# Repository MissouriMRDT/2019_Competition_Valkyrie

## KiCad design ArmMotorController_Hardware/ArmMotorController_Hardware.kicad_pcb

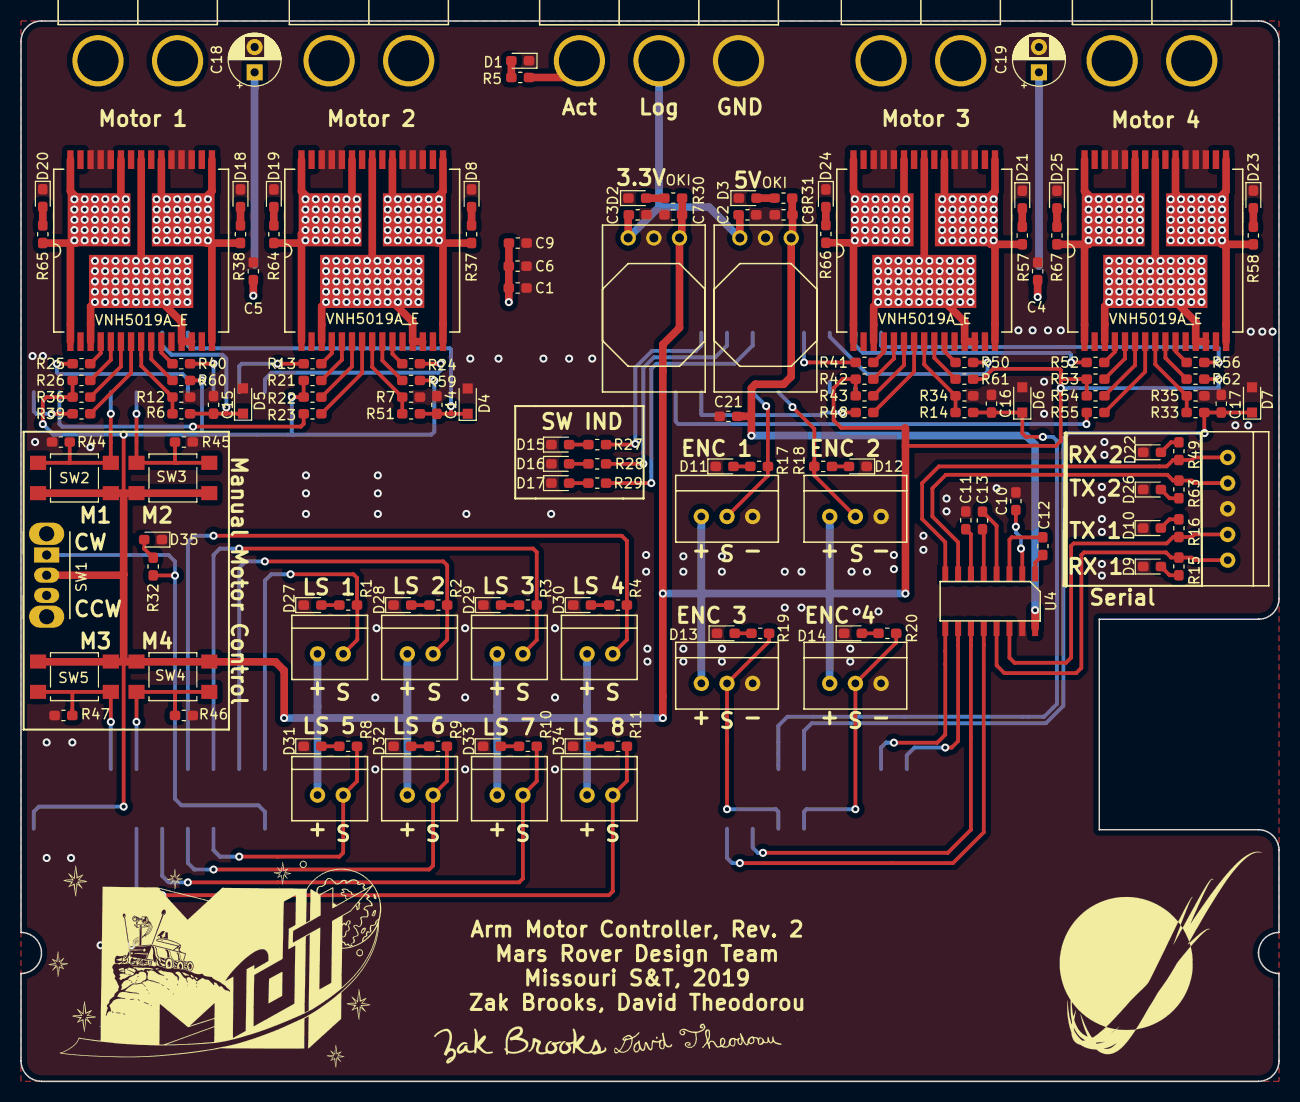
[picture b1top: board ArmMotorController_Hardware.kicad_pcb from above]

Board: 2 copper layers, 124.5 x 104.9 mm, 153 parts (0 on the bottom side), 122 nets.

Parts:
C1, C10, C11, C12, C13: .1u; C_0603_1608Metric_Pad1.05x0.95mm_HandSolder
C2, C3, C4, C5, C6, C7, C8, C9: 10u; C_0603_1608Metric_Pad1.05x0.95mm_HandSolder
C14, C15, C16, C17: 33nF; C_0603_1608Metric_Pad1.05x0.95mm_HandSolder
C18, C19: 47u; CP_Radial_D5.0mm_P2.50mm
C21: 10uF; C_0603_1608Metric_Pad1.05x0.95mm_HandSolder
Conn1: Anderson-3; Anderson_3_Horizontal_Side_by_Side
Conn3: Limit_Switch_1; MOLEX_SL_02_Vertical
Conn4: Limit_Switch_2; MOLEX_SL_02_Vertical
Conn5: Limit_Switch_3; MOLEX_SL_02_Vertical
Conn6: Limit_Switch_4; MOLEX_SL_02_Vertical
Conn7: Limit_Switch_5; MOLEX_SL_02_Vertical
Conn8: Limit_Switch_6; MOLEX_SL_02_Vertical
Conn9: Limit_Switch_7; MOLEX_SL_02_Vertical
Conn10: Limit_Switch_8; MOLEX_SL_02_Vertical
Conn11: Molex_SL_05; MOLEX_SL_05_Vertical
Conn12: Encoder_1; MOLEX_SL_03_Vertical
Conn13: Encoder_2; MOLEX_SL_03_Vertical
Conn14: Encoder_3; MOLEX_SL_03_Vertical
Conn15: Encoder_4; MOLEX_SL_03_Vertical
Conn16, Conn17, Conn18, Conn19: AndersonPP; Anderson_2_Horizontal_Side_by_Side
D1, D2, D3, D8, D9, D10, D11, D12, D13, D14, D15, D16, D17, D18, D19, D20, D21, D22, D23, D24, D25, D26, D27, D28, D29, D30, D31, D32, D33, D34, D35: LED; LED_0603_1608Metric_Pad1.05x0.95mm_HandSolder
D4, D5, D6, D7: D_Zener; D_SOD-323_HandSoldering
R1, R2, R3, R4, R5, R8, R9, R10, R11, R15, R16, R17, R18, R19, R20, R27, R28, R29, R30, R31, R32, R44, R45, R46, R47, R49, R63: 500; R_0603_1608Metric_Pad1.05x0.95mm_HandSolder
R6, R14, R33, R51: 10k; R_0603_1608Metric_Pad1.05x0.95mm_HandSolder
R7, R12, R13, R21, R23, R24, R25, R26, R34, R35, R39, R40, R41, R42, R48, R50, R52, R53, R55, R56, R59, R60, R61, R62: 1k; R_0603_1608Metric_Pad1.05x0.95mm_HandSolder
R22, R36, R43, R54: 0; R_0603_1608Metric_Pad1.05x0.95mm_HandSolder
R37, R38, R57, R58, R64, R65, R66, R67: 1.5k; R_0603_1608Metric_Pad1.05x0.95mm_HandSolder
SW1: SW_SPDT; SW_CuK_OS102011MA1QN1_SPDT_Angled
SW2, SW3, SW4, SW5: SW_Push; SW_SPST_TL3305A
U1, U2: OKI; OKI_Horizontal
U3: TM4C129E_Launchpad; TM4C129E_Launchpad_FULL_SMD_BOTTOM
U4: MAX_3232; SOIC_16_3.9x9.9mm_Pitch1.27mm
U5, U6, U7, U8: VNH5019A_E; MultiPowerSO_30

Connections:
12vLog: C2.2, C3.2, Conn1.2, U1.1, U2.1
+3V3: C7.2, Conn3.1, Conn4.1, Conn5.1, Conn6.1, Conn7.1, Conn8.1, Conn9.1, Conn10.1, Conn12.1, Conn13.1, Conn14.1, Conn15.1, R21.2, R22.2, R26.2, R30.2, R36.2, R42.2, R43.2, R53.2, R54.2, R59.2, R60.2, R61.2, R62.2, SW1.2, SW2.1, SW3.1, SW4.1, SW5.1, U1.3, U3.+3V3
+5V: C8.2, C21.2, R31.2, U2.3, U4.16
+12V: C1.1, C4.1, C5.1, C6.1, C9.1, C18.1, C19.1, Conn1.3, R5.2, U5.3, U5.12, U5.13, U5.23, U5.32, U6.3, U6.12, U6.13, U6.23, U6.32, U7.3, U7.12, U7.13, U7.23, U7.32, U8.3, U8.12, U8.13, U8.23, U8.32
/Out_A_M1: Conn16.2, R65.2, U5.1, U5.25, U5.30, U5.31
/Out_A_M2: Conn17.2, R64.2, U6.1, U6.25, U6.30, U6.31
/Out_A_M3: Conn18.2, R66.2, U7.1, U7.25, U7.30, U7.31
/Out_A_M4: Conn19.2, R67.2, U8.1, U8.25, U8.30, U8.31
/Out_B_M1: Conn16.1, R38.2, U5.15, U5.16, U5.21, U5.33
/Out_B_M2: Conn17.1, R37.1, U6.15, U6.16, U6.21, U6.33
/Out_B_M3: Conn18.1, R57.1, U7.15, U7.16, U7.21, U7.33
/Out_B_M4: Conn19.1, R58.2, U8.15, U8.16, U8.21, U8.33
DIRECTION_SW: R32.1, SW1.1, U3.PB3
ENC_1_PWM: Conn12.2, R17.2, U3.PM0
ENC_2_PWM: Conn13.2, R18.2, U3.PM1
ENC_3_PWM: Conn14.2, R19.2, U3.PD4
ENC_4_PWM: Conn15.2, R20.2, U3.PD5
GND: C1.2, C2.1, C3.1, C4.2, C5.2, C6.2, C7.1, C8.1, C9.2, C10.2, C11.2, C14.2, C15.2, C16.2, C17.2, C18.2, C19.2, C21.1, Conn1.1, Conn11.3, Conn12.3, Conn13.3, Conn14.3, Conn15.3, D1.1, D2.1, D3.1, D4.2, D5.2, D6.2, D7.2, D8.1, D9.1, D10.1, D11.1, D12.1, D13.1, D14.1, D15.1, D16.1, D17.1, D18.1, D19.1, D20.1, D21.1, D22.1, D23.1, D24.1, D25.1, D26.1, D27.1, D28.1, D29.1, D30.1, D31.1, D32.1, D33.1, D34.1, D35.1, R7.1, R12.1, R34.1, R35.1, R44.1, R45.1, R46.1, R47.1, U1.2, U2.2, U3.GND, U4.15, U5.18, U5.19, U5.20, U5.26, U5.27, U5.28, U6.18, U6.19, U6.20, U6.26, U6.27, U6.28, U7.18, U7.19, U7.20, U7.26, U7.27, U7.28, U8.18, U8.19, U8.20, U8.26, U8.27, U8.28
IN_A1: R25.2, U3.PL0
IN_A2: R13.2, U3.PL2
IN_A3: R41.2, U3.PQ2
IN_A4: R52.2, U3.PP3
IN_B1: R40.2, U3.PL1
IN_B2: R24.2, U3.PL3
IN_B3: R50.2, U3.PQ3
IN_B4: R56.2, U3.PQ1
I_SENSE_1: C15.1, D5.1, R6.1, U3.PD1
I_SENSE_2: C14.1, D4.1, R51.1, U3.PD0
I_SENSE_3: C16.1, D6.1, R14.1, U3.PK0
I_SENSE_4: C17.1, D7.1, R33.1, U3.PK1
LED_IND_SW_1: R27.2, U3.PM7
LED_IND_SW_2: R28.2, U3.PP5
LED_IND_SW_ERR: R29.2, U3.PA7
LS_1: Conn3.2, R1.2, U3.PM5
LS_2: Conn4.2, R2.2, U3.PM4
LS_3: Conn5.2, R3.2, U3.PA6
LS_4: Conn6.2, R4.2, U3.PD7
LS_5: Conn7.2, R8.2, U3.PC7
LS_6: Conn8.2, R9.2, U3.PD3
LS_7: Conn9.2, R10.2, U3.PE5
LS_8: Conn10.2, R11.2, U3.PC6
M1_PWM: R39.2, U3.PF1
M1_SW: R44.2, SW2.2, U3.PG0
M2_PWM: R23.2, U3.PF2
M2_SW: R45.2, SW3.2, U3.PL4
M3_PWM: R48.2, U3.PK4
M3_SW: R47.2, SW5.2, U3.PE1
M4_PWM: R55.2, U3.PG1
M4_SW: R46.2, SW4.2, U3.PE2
unnamed: C10.1, U4.2
unnamed: C11.1, U4.6
unnamed: C12.1, U4.1
unnamed: C12.2, U4.3
unnamed: C13.1, U4.4
unnamed: C13.2, U4.5
unnamed: D1.2, R5.1
unnamed: D2.2, R30.1
unnamed: D3.2, R31.1
unnamed: D8.2, R37.2
unnamed: D9.2, R15.1
unnamed: D10.2, R16.1
unnamed: D11.2, R17.1
unnamed: D12.2, R18.1
unnamed: D13.2, R19.1
unnamed: D14.2, R20.1
unnamed: D15.2, R27.1
unnamed: D16.2, R28.1
unnamed: D17.2, R29.1
unnamed: D18.2, R38.1
unnamed: D19.2, R64.1
unnamed: D20.2, R65.1
unnamed: D21.2, R57.2
unnamed: D22.2, R49.1
unnamed: D23.2, R58.1
unnamed: D24.2, R66.1
unnamed: D25.2, R67.1
unnamed: D26.2, R63.1
unnamed: D27.2, R1.1
unnamed: D28.2, R2.1
unnamed: D29.2, R3.1
unnamed: D30.2, R4.1
unnamed: D31.2, R8.1
unnamed: D32.2, R9.1
unnamed: D33.2, R10.1
unnamed: D34.2, R11.1
unnamed: D35.2, R32.2
unnamed: R6.2, R12.2, U5.8
unnamed: R13.1, U6.4
unnamed: R14.2, R34.2, U7.8
unnamed: R21.1, U6.5
unnamed: R22.1, U6.6
unnamed: R23.1, U6.7
unnamed: R24.1, U6.10
unnamed: R25.1, U5.4
unnamed: R26.1, U5.5
unnamed: R33.2, R35.2, U8.8
unnamed: R36.1, U5.6
unnamed: R39.1, U5.7
unnamed: R40.1, U5.10
unnamed: R41.1, U7.4
unnamed: R42.1, U7.5
unnamed: R43.1, U7.6
unnamed: R48.1, U7.7
unnamed: R50.1, U7.10
unnamed: R7.2, R51.2, U6.8
unnamed: R52.1, U8.4
unnamed: R53.1, U8.5
unnamed: R54.1, U8.6
unnamed: R55.1, U8.7
unnamed: R56.1, U8.10
unnamed: R59.1, U6.9
unnamed: R60.1, U5.9
unnamed: R61.1, U7.9
unnamed: R62.1, U8.9
RX_1_SL: Conn11.5, R15.2, U4.13
RX_1_Tiva: U3.PP0, U4.12
RX_2_SL: Conn11.1, R49.2, U4.8
RX_2_Tiva: U3.PA4, U4.9
TX_1_SL: Conn11.4, R16.2, U4.14
TX_1_Tiva: U3.PP1, U4.11
TX_2_SL: Conn11.2, R63.2, U4.7
TX_2_Tiva: U3.PA5, U4.10

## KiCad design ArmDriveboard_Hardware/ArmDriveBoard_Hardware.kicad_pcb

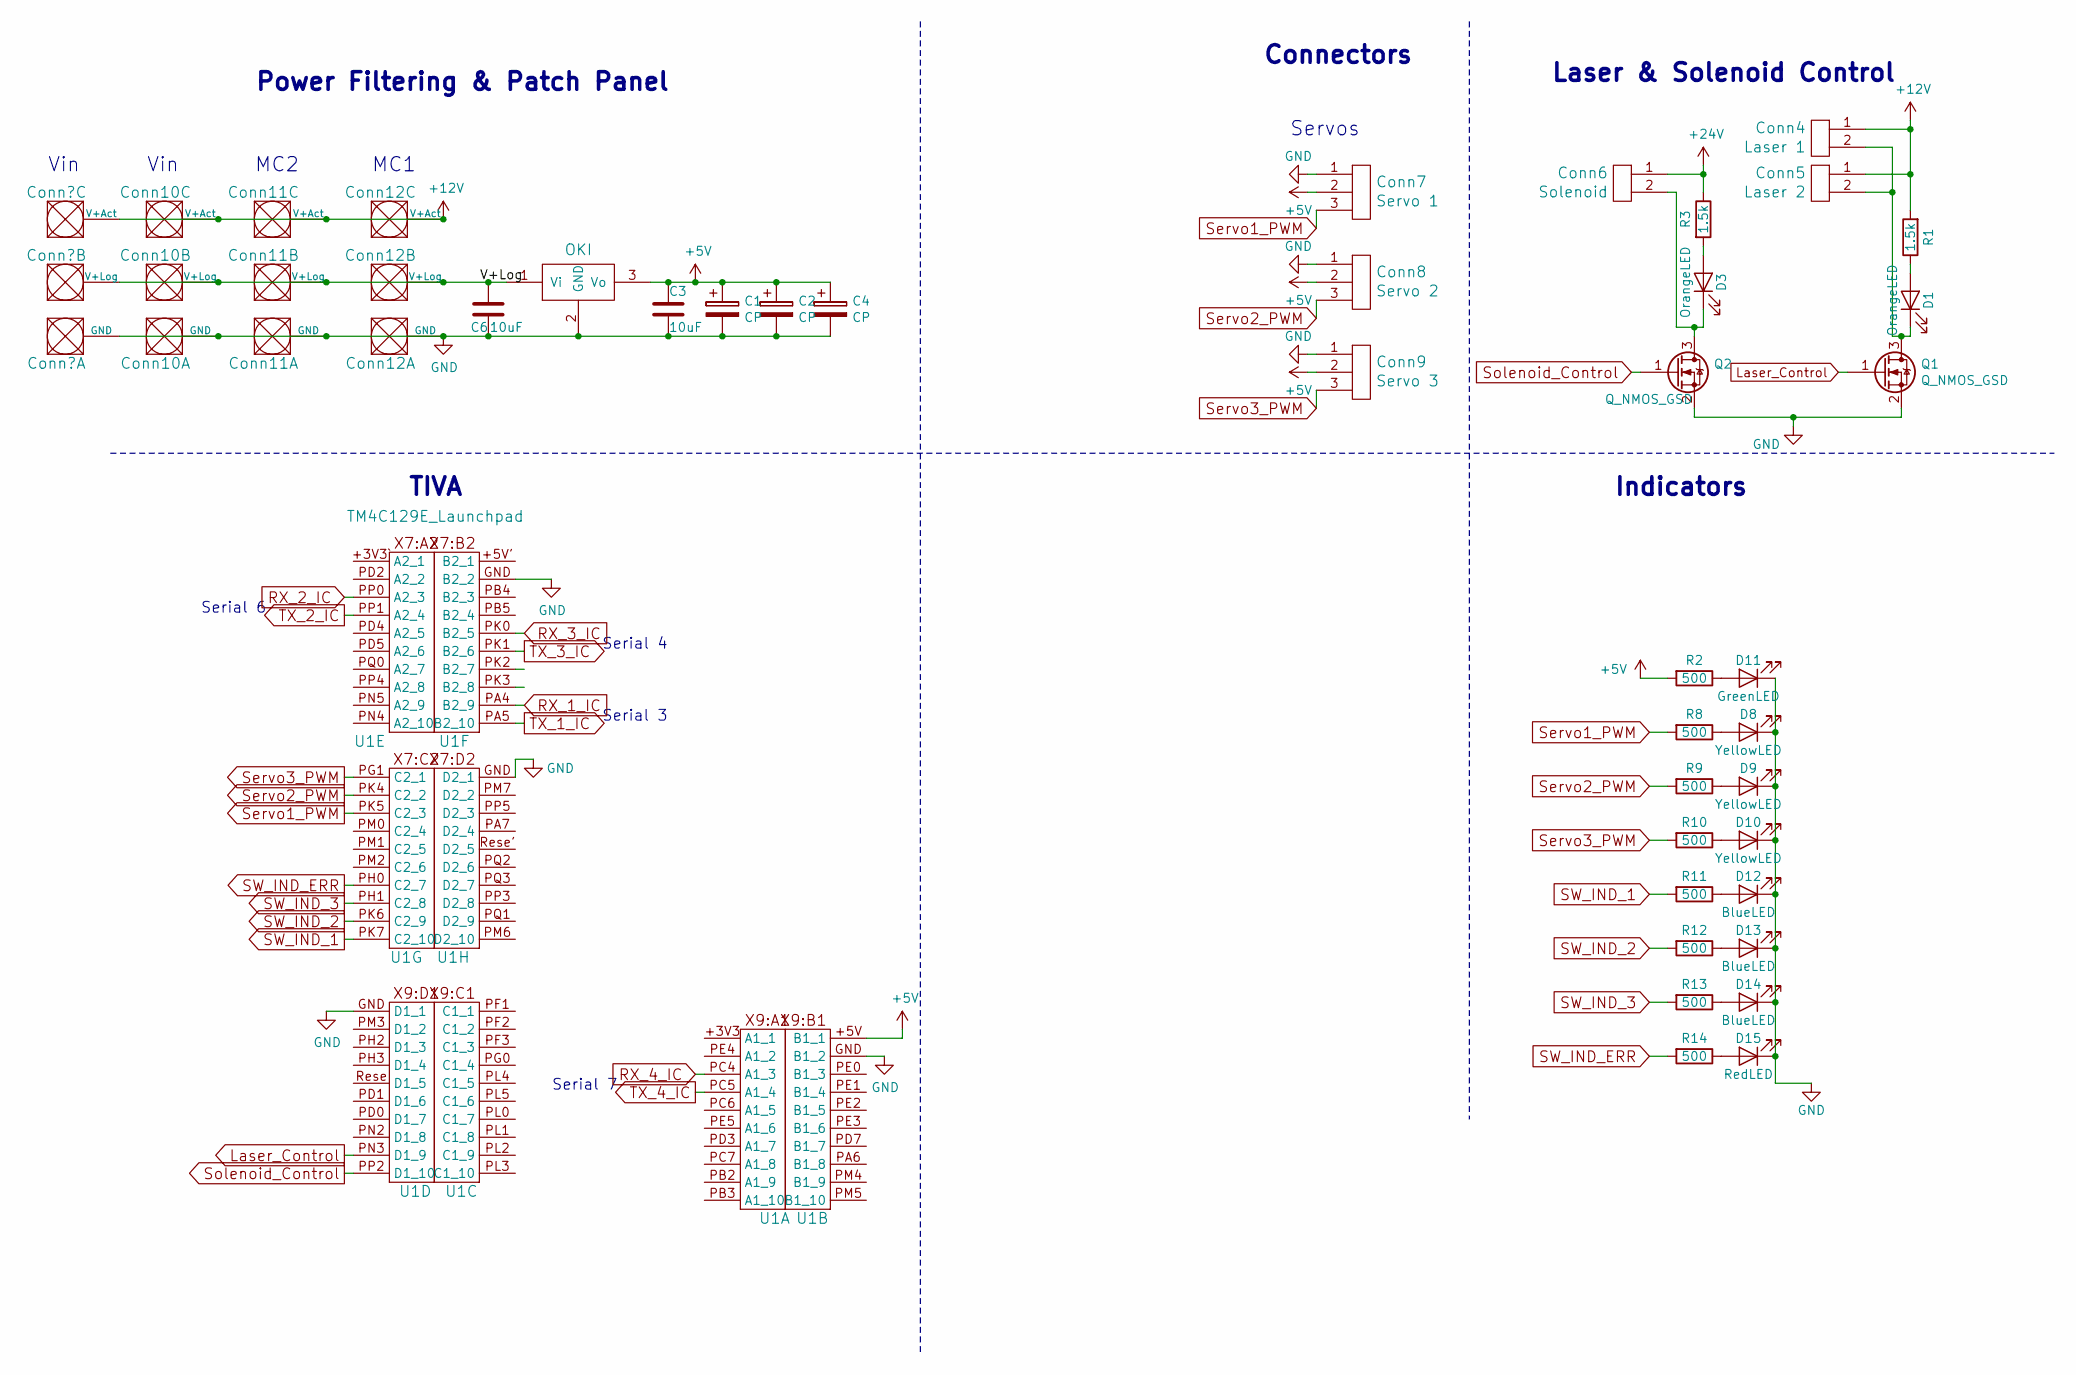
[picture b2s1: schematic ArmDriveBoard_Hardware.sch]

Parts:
C1, C2, C4: CP; CP_Radial_D8.0mm_P3.50mm
C3, C6: 10uF; C_0603_1608Metric_Pad1.05x0.95mm_HandSolder
Conn4: Laser 1; MOLEX_SL_02_Vertical
Conn5: Laser 2; MOLEX_SL_02_Vertical
Conn6: Solenoid; MOLEX_SL_02_Vertical
Conn7: Servo 1; MOLEX_SL_03_Vertical
Conn8: Servo 2; MOLEX_SL_03_Vertical
Conn9: Servo 3; MOLEX_SL_03_Vertical
Conn10, Conn11, Conn12: AndersonPP; Anderson_3_Vertical_Side_by_Side
D1, D3: OrangeLED; LED_0603_1608Metric_Pad1.05x0.95mm_HandSolder
D8, D9, D10: YellowLED; LED_0603_1608Metric_Pad1.05x0.95mm_HandSolder
D11: GreenLED; LED_0603_1608Metric_Pad1.05x0.95mm_HandSolder
D12, D13, D14: BlueLED; LED_0603_1608Metric_Pad1.05x0.95mm_HandSolder
D15: RedLED; LED_0603_1608Metric_Pad1.05x0.95mm_HandSolder
Q1, Q2: Q_NMOS_GSD; SOT-23
R1, R3: 1.5k; R_0603_1608Metric_Pad1.05x0.95mm_HandSolder
R2, R8, R9, R10, R11, R12, R13, R14: 500; R_0603_1608Metric_Pad1.05x0.95mm_HandSolder
U1: TM4C129E_Launchpad; TM4C129E_Launchpad_FULL_THT_BOTTOM
U3: OKI; OKI_Horizontal

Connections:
+5V: C1.1, C2.1, C3.1, C4.1, Conn7.2, Conn8.2, Conn9.2, R2.2, U1.+5V (B1_1), U3.3 (Vo)
+12V: Conn4.1, Conn5.1, Conn10.3 (V+Act), Conn11.3 (V+Act), Conn12.3 (V+Act), R1.2; also elsewhere on the board
+24V: Conn6.1, R3.1
/V+Log: C6.2, Conn10.2 (V+Log), Conn11.2 (V+Log), Conn12.2 (V+Log), U3.1 (Vi); also elsewhere on the board
GND: C1.2, C2.2, C3.2, C4.2, C6.1, Conn7.1, Conn8.1, Conn9.1, Conn10.1 (GND), Conn11.1 (GND), Conn12.1 (GND), D8.1 (K), D9.1 (K), D10.1 (K), D11.1 (K), D12.1 (K), D13.1 (K), D14.1 (K), D15.1 (K), Q1.2 (S), Q2.2 (S), U1.GND (B1_2), U3.2 (GND); also elsewhere on the board
Laser_Control: Q1.1 (G), U1.PN3 (D1_9)
unnamed: Conn4.2, Conn5.2, D1.1 (K), Q1.3 (D)
unnamed: Conn6.2, D3.1 (K), Q2.3 (D)
unnamed: D1.2 (A), R1.1
unnamed: D3.2 (A), R3.2
unnamed: D8.2 (A), R8.1
unnamed: D9.2 (A), R9.1
unnamed: D10.2 (A), R10.1
unnamed: D11.2 (A), R2.1
unnamed: D12.2 (A), R11.1
unnamed: D13.2 (A), R12.1
unnamed: D14.2 (A), R13.1
unnamed: D15.2 (A), R14.1
RX_1_IC: U1.PA4 (B2_9)
RX_2_IC: U1.PP0 (A2_3)
RX_3_IC: U1.PK0 (B2_5)
RX_4_IC: U1.PC4 (A1_3)
SW_IND_1: R11.2, U1.PK7 (C2_10)
SW_IND_2: R12.2, U1.PK6 (C2_9)
SW_IND_3: R13.2, U1.PH1 (C2_8)
SW_IND_ERR: R14.2, U1.PH0 (C2_7)
Servo1_PWM: Conn7.3, R8.2, U1.PK5 (C2_3)
Servo2_PWM: Conn8.3, R9.2, U1.PK4 (C2_2)
Servo3_PWM: Conn9.3, R10.2, U1.PG1 (C2_1)
Solenoid_Control: Q2.1 (G), U1.PP2 (D1_10)
TX_1_IC: U1.PA5 (B2_10)
TX_2_IC: U1.PP1 (A2_4)
TX_3_IC: U1.PK1 (B2_6)
TX_4_IC: U1.PC5 (A1_4)

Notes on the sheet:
Serial 6
Serial 3
TIVA
Power Filtering & Patch Panel
Connectors
Laser & Solenoid Control
MC1
MC2
Vin
Servos
Indicators
Serial 4
Serial 7

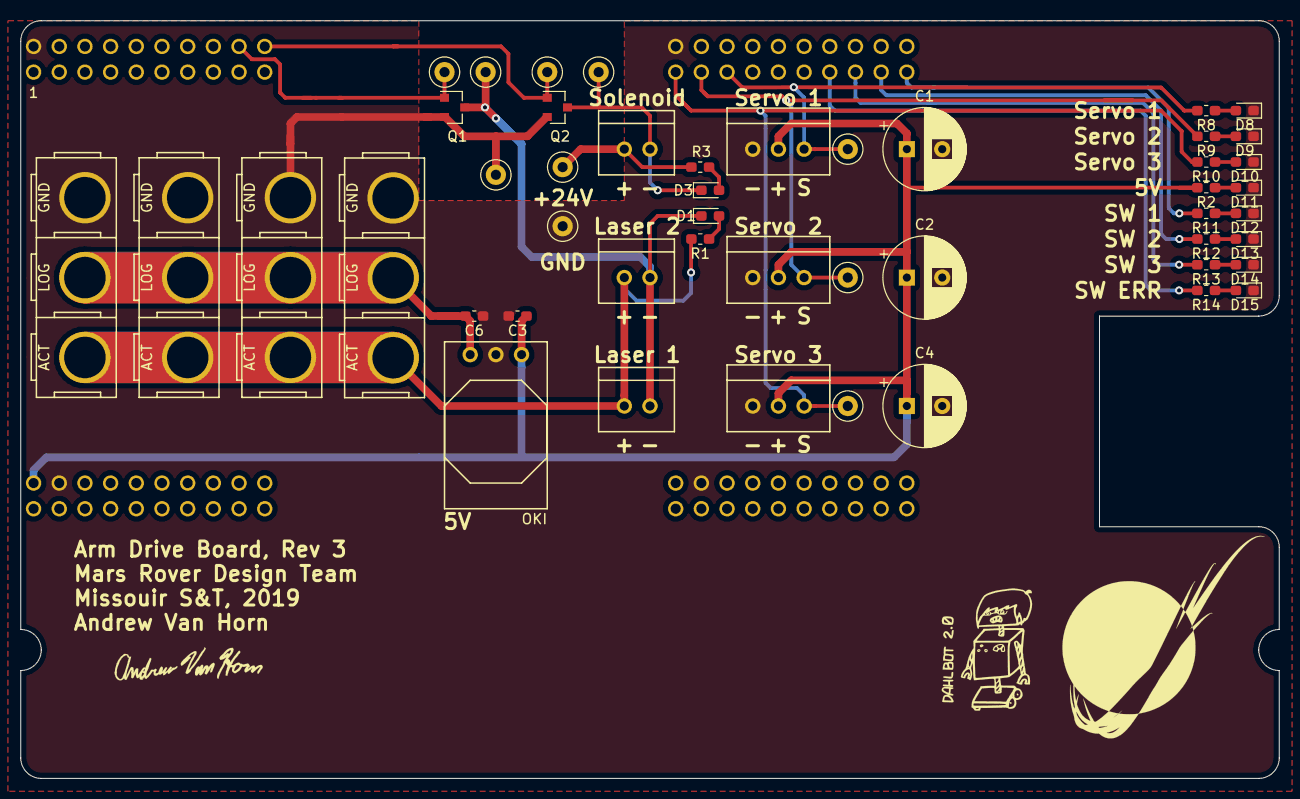
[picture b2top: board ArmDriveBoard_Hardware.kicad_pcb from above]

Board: 2 copper layers, 124.5 x 74.9 mm, 39 parts (0 on the bottom side), 26 nets.

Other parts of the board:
Conn1: AndersonPP; Anderson_3_Vertical_Side_by_Side

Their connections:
+12V: Conn1.3; also elsewhere on the board
/V+Log: Conn1.2; also elsewhere on the board
GND: Conn1.1; also elsewhere on the board

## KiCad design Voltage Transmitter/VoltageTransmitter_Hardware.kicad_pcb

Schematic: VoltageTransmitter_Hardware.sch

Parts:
C1, C2: 10uF; C_0603_1608Metric_Pad1.05x0.95mm_HandSolder
Conn1: AndersonPP-MRDT_Connectors; Anderson_2_Horizontal_Stacked
Conn2: Molex_SL_02; MOLEX_SL_02_Horizontal
D1, D2: LED; LED_0603_1608Metric_Pad1.05x0.95mm_HandSolder
R1: 150K; R_0603_1608Metric_Pad1.05x0.95mm_HandSolder
R2: 15K; R_0603_1608Metric_Pad1.05x0.95mm_HandSolder
R3, R4: 500; R_0603_1608Metric_Pad1.05x0.95mm_HandSolder
SW1: SW_Push_SPDT; SW_CuK_OS102011MA1QN1_SPDT_Angled
U1: OKI; OKI_Horizontal
U2: ESP8266_MCU; ESP_8266 NODEMCU

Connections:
+3V3: C2.1, R3.1, U1.3, U2.11 (3v3), U2.16 (3v3)
Din: R1.2, R2.1, U2.1 (A0)
GND: C1.2, C2.2, Conn1.2 (V+Log), Conn2.1, D1.1, D2.1, R2.2, U1.2, U2.10 (GND), U2.24 (GND)
unnamed: C1.1, SW1.2, U1.1
unnamed: Conn1.1 (GND), R1.1
unnamed: Conn2.2, SW1.3
unnamed: D1.2, R3.2
unnamed: D2.2, R4.2
TX_IND: R4.1, U2.30 (D0)

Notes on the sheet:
9V Battery
Voltage Sensing
Power Input
ESP8266-12e
Green
Blue
Indication
Switched andersons so that they properly mate with the andersons on the batt packs

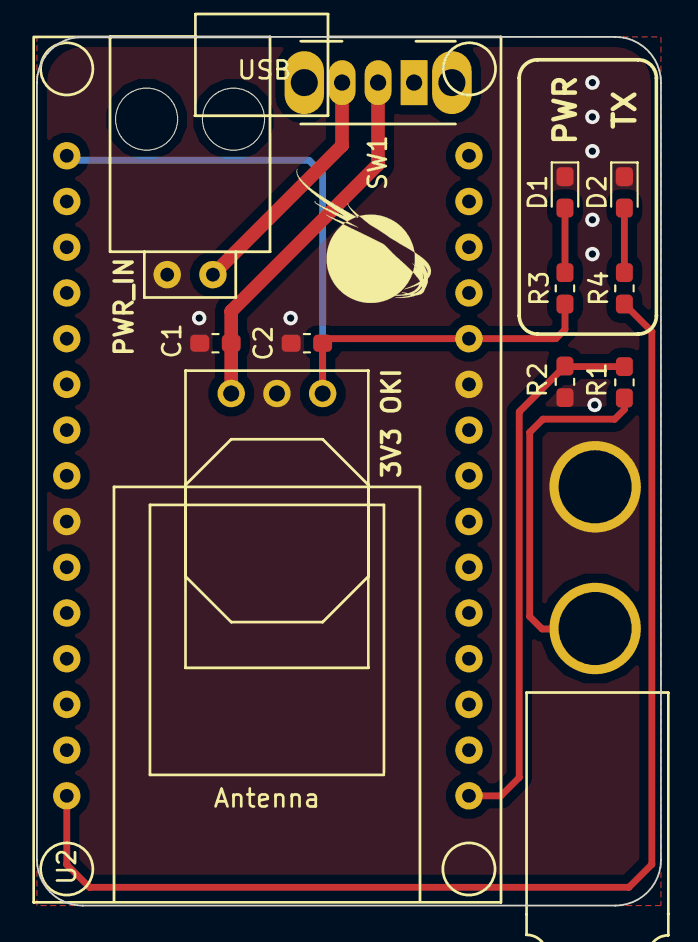
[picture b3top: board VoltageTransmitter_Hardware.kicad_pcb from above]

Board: 2 copper layers, 34.7 x 48.3 mm, 13 parts (0 on the bottom side), 9 nets.

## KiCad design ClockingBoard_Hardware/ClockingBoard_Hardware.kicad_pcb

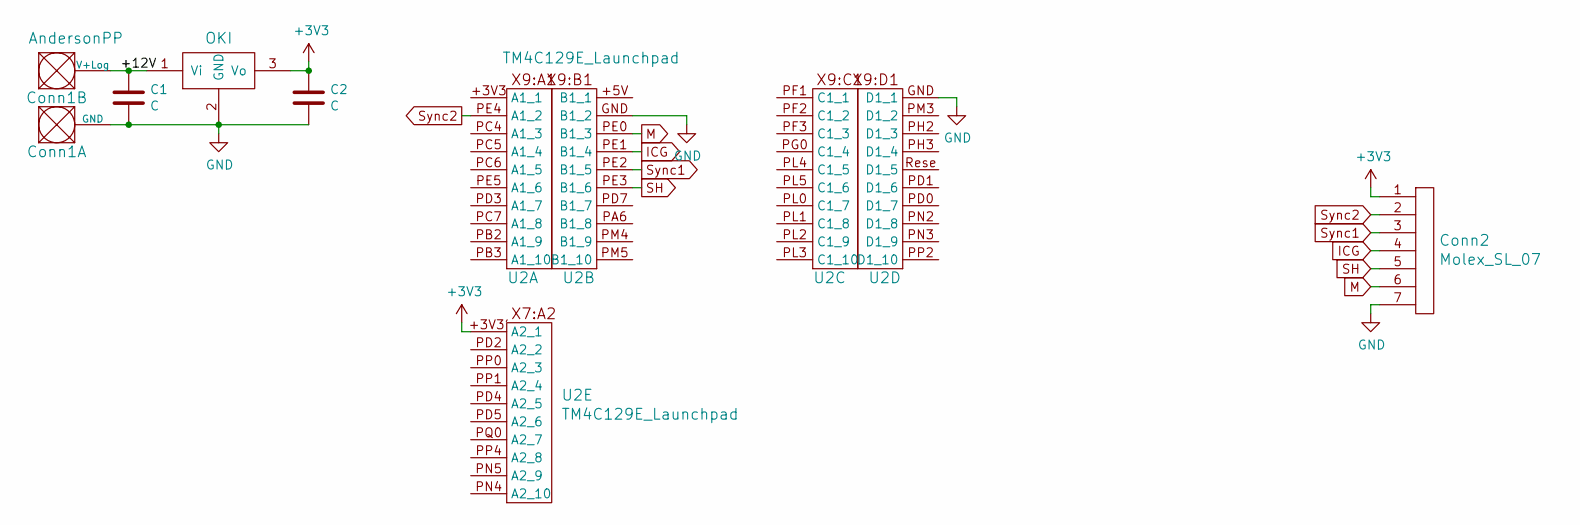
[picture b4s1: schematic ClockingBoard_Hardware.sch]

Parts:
C1, C2: C; C_0603_1608Metric_Pad1.05x0.95mm_HandSolder
Conn1: AndersonPP; Anderson_2_Horizontal_Side_by_Side
Conn2: Molex_SL_07; MOLEX_SL_07_Vertical
U1: OKI; OKI_Horizontal
U2: TM4C129E_Launchpad

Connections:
+3V3: C2.1, Conn2.1, U1.3 (Vo), U2.+3V3' (A2_1)
/+12V: C1.1, Conn1.2 (V+Log), U1.1 (Vi)
GND: C1.2, C2.2, Conn1.1 (GND), Conn2.7, U1.2 (GND), U2.GND (B1_2)
ICG: Conn2.4, U2.PE1 (B1_4)
M: Conn2.6, U2.PE0 (B1_3)
SH: Conn2.5, U2.PE3 (B1_6)
Sync1: Conn2.3, U2.PE2 (B1_5)
Sync2: Conn2.2, U2.PE4 (A1_2)

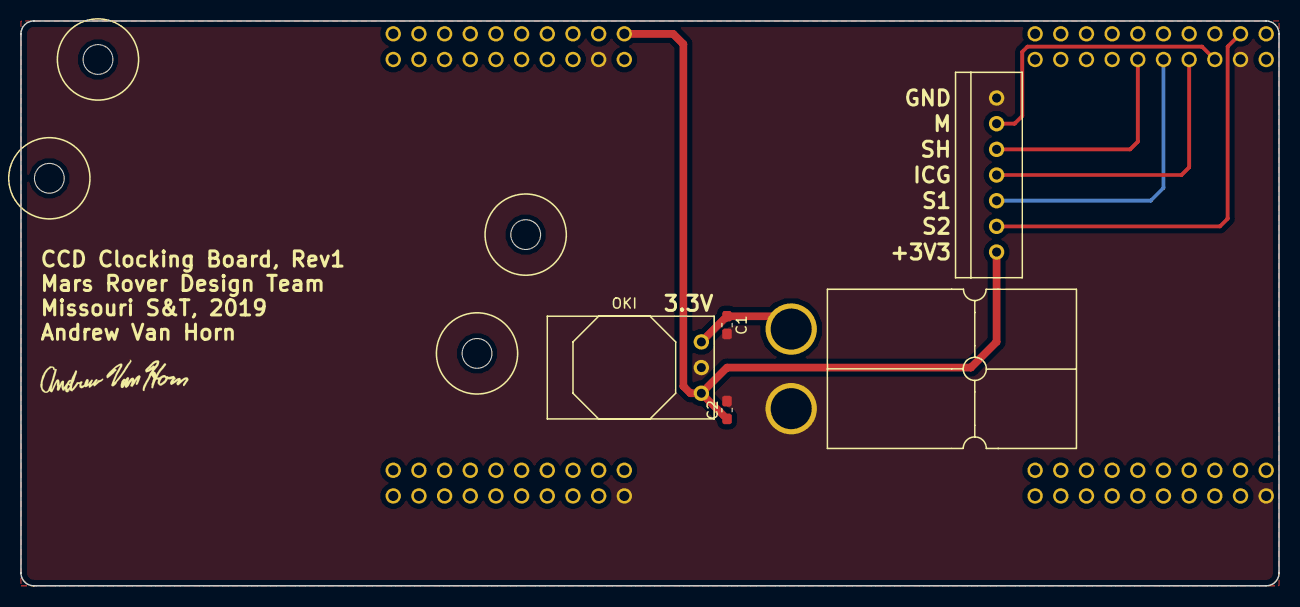
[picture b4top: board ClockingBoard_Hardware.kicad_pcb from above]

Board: 2 copper layers, 124.5 x 55.9 mm, 6 parts (0 on the bottom side), 8 nets.

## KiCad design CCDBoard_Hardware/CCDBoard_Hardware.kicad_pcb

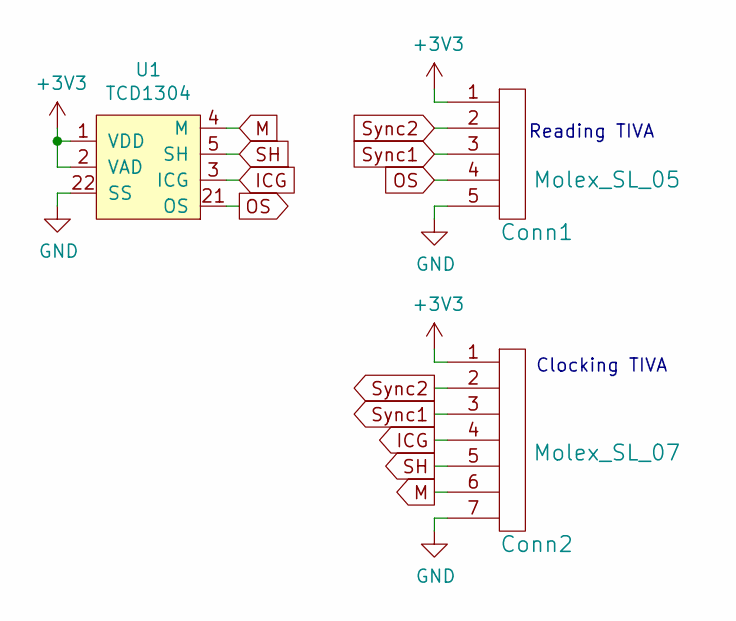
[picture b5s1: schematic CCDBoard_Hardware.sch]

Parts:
Conn1: Molex_SL_05; MOLEX_SL_05_Vertical
Conn2: Molex_SL_07; MOLEX_SL_07_Vertical
U1: TCD1304; TCD-1304

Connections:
+3V3: Conn1.1, Conn2.1, U1.1 (VDD), U1.2 (VAD)
GND: Conn1.5, Conn2.7, U1.22 (SS)
ICG: Conn2.4, U1.3 (ICG)
M: Conn2.6, U1.4 (M)
OS: Conn1.4, U1.21 (OS)
SH: Conn2.5, U1.5 (SH)
Sync1: Conn1.3, Conn2.3
Sync2: Conn1.2, Conn2.2

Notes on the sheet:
Clocking TIVA
Reading TIVA

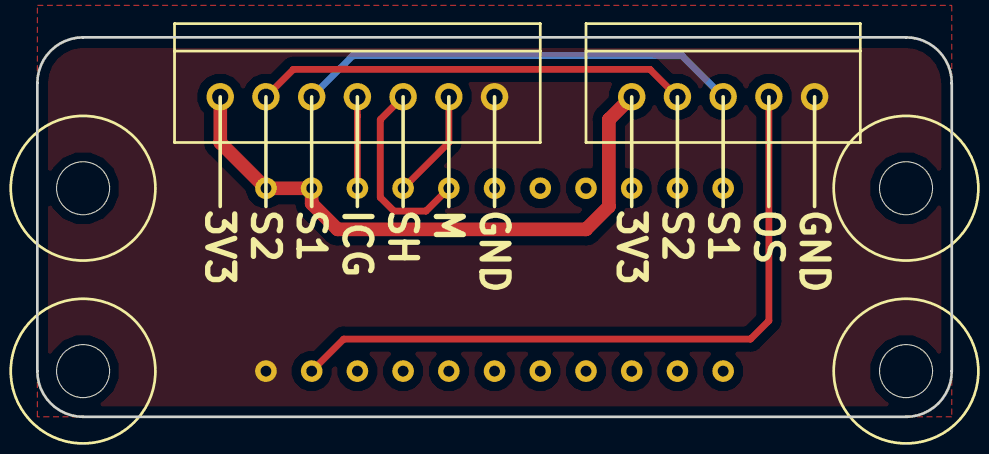
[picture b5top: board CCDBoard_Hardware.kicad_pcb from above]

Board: 2 copper layers, 50.8 x 21.1 mm, 3 parts (1 on the bottom side), 8 nets.

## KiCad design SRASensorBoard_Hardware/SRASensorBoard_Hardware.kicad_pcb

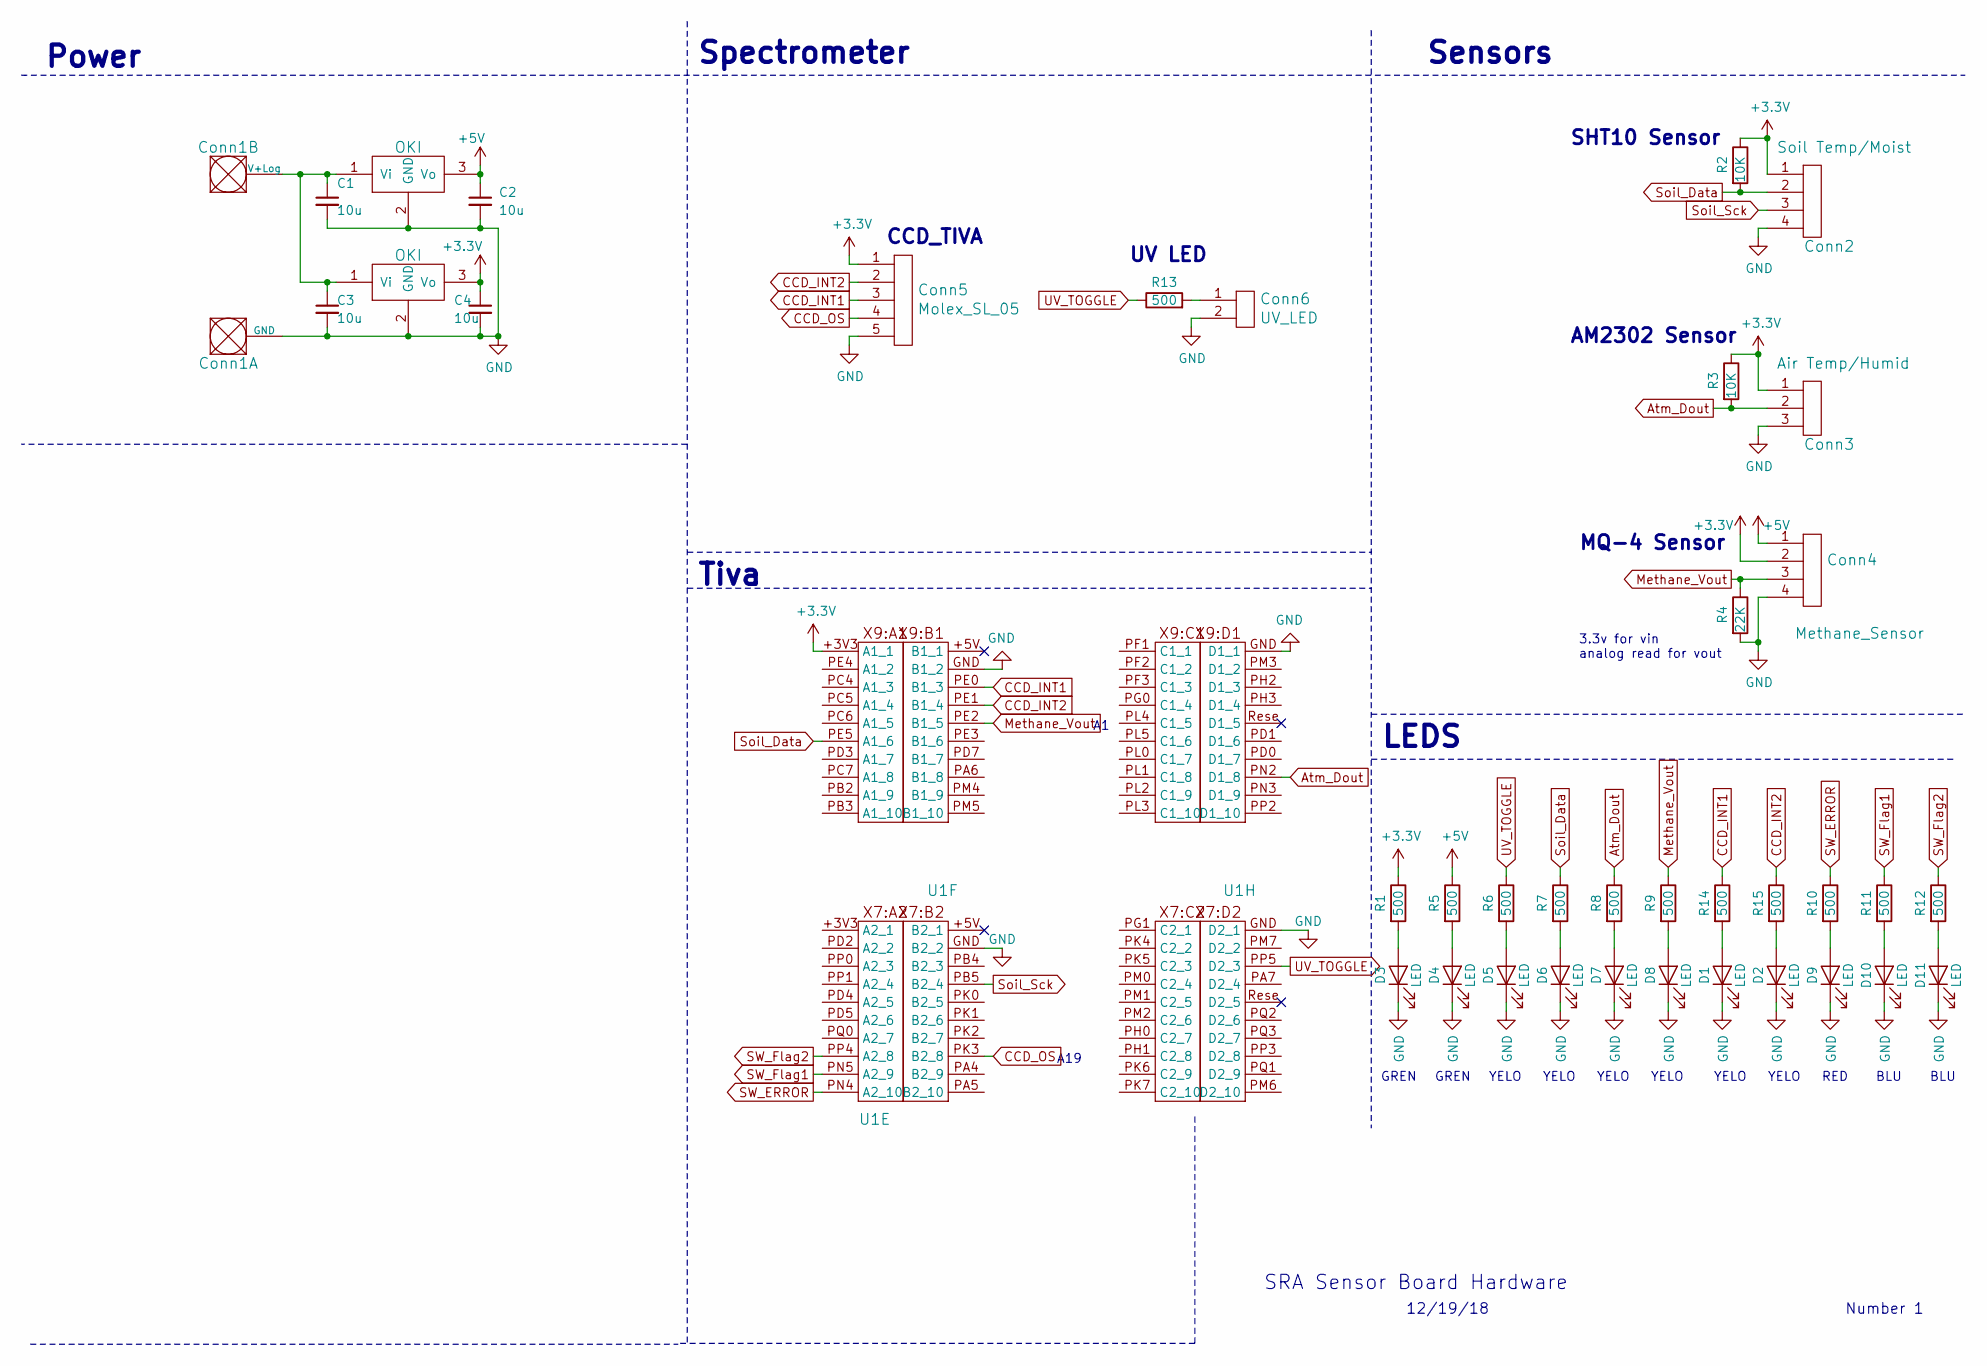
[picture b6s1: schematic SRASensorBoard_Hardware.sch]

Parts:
C1, C2, C3, C4: 10u; C_0603_1608Metric_Pad1.05x0.95mm_HandSolder
Conn1: AndersonPP; Anderson_2_Horisontal_Side_by_Side
Conn2: Soil Temp/Moist; MOLEX_SL_04_Vertical
Conn3: Air Temp/Humid; MOLEX_SL_03_Vertical
Conn4: Methane_Sensor; MOLEX_SL_04_Vertical
Conn5: Molex_SL_05; MOLEX_SL_05_Vertical
Conn6: UV_LED; MOLEX_SL_02_Vertical
D1, D2, D3, D4, D5, D6, D7, D8, D9, D10, D11: LED; D_0603_1608Metric_Pad1.05x0.95mm_HandSolder
R1, R5, R6, R7, R8, R9, R10, R11, R12, R13, R14, R15: 500; R_0603_1608Metric_Pad1.05x0.95mm_HandSolder
R2, R3: 10K; R_0603_1608Metric_Pad1.05x0.95mm_HandSolder
R4: 22K; R_0603_1608Metric_Pad1.05x0.95mm_HandSolder
U1: Tive Header; TM4C129E_Launchpad_FULL
U2, U3: OKI; OKI_Horizontal

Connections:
+3V3: C4.1, Conn2.1, Conn3.1, Conn4.2, Conn5.1, R1.1, R2.1, R3.1, U1.+3V3 (A1_1), U3.3 (Vo)
+5V: C2.1, Conn4.1, R5.1, U2.3 (Vo)
Atm_Dout: Conn3.2, R3.2, R8.1, U1.PN2 (D1_8)
CCD_INT1: Conn5.3, R14.1, U1.PE0 (B1_3)
CCD_INT2: Conn5.2, R15.1, U1.PE1 (B1_4)
CCD_OS: Conn5.4, U1.PK3 (B2_8)
GND: C1.2, C2.2, C3.2, C4.2, Conn1.1 (GND), Conn2.4, Conn3.3, Conn4.4, Conn5.5, Conn6.2, D1.1 (K), D2.1 (K), D3.1 (K), D4.1 (K), D5.1 (K), D6.1 (K), D7.1 (K), D8.1 (K), D9.1 (K), D10.1 (K), D11.1 (K), R4.2, U1.GND (B1_2), U2.2 (GND), U3.2 (GND)
Methane_Vout: Conn4.3, R4.1, R9.1, U1.PE2 (B1_5)
unnamed: C1.1, C3.1, Conn1.2 (V+Log), U2.1 (Vi), U3.1 (Vi)
unnamed: Conn6.1, R13.2
unnamed: D1.2 (A), R14.2
unnamed: D2.2 (A), R15.2
unnamed: D3.2 (A), R1.2
unnamed: D4.2 (A), R5.2
unnamed: D5.2 (A), R6.2
unnamed: D6.2 (A), R7.2
unnamed: D7.2 (A), R8.2
unnamed: D8.2 (A), R9.2
unnamed: D9.2 (A), R10.2
unnamed: D10.2 (A), R11.2
unnamed: D11.2 (A), R12.2
SW_ERROR: R10.1, U1.PN4 (A2_10)
SW_Flag1: R11.1, U1.PN5 (A2_9)
SW_Flag2: R12.1, U1.PP4 (A2_8)
Soil_Data: Conn2.2, R2.2, R7.1, U1.PE5 (A1_6)
Soil_Sck: Conn2.3, U1.PB5 (B2_4)
UV_TOGGLE: R6.1, R13.1, U1.PP5 (D2_3)

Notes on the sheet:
Sensors
Power
3.3v for vin analog read for vout
Spectrometer
CCD_TIVA
UV LED
SHT10 Sensor
AM2302 Sensor
MQ-4 Sensor
LEDS
Tiva
RED
BLU
GREN
YELO
12/19/18
SRA Sensor Board Hardware
Number 1
A19
YELO

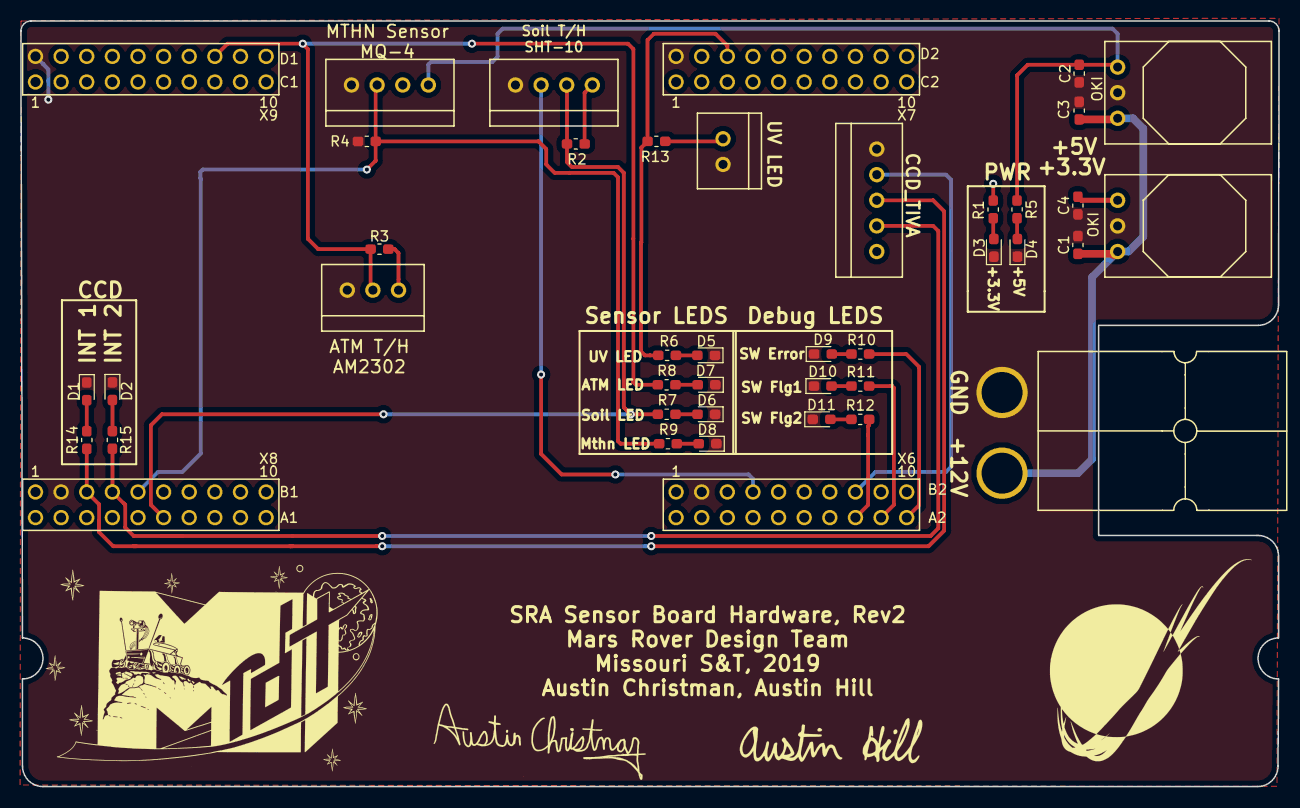
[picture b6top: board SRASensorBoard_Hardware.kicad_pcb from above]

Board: 2 copper layers, 124.7 x 75.9 mm, 39 parts (0 on the bottom side), 27 nets.

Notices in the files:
parts and their libraries:
Copyright 2016 Accelerated Designs. All rights reserved.
